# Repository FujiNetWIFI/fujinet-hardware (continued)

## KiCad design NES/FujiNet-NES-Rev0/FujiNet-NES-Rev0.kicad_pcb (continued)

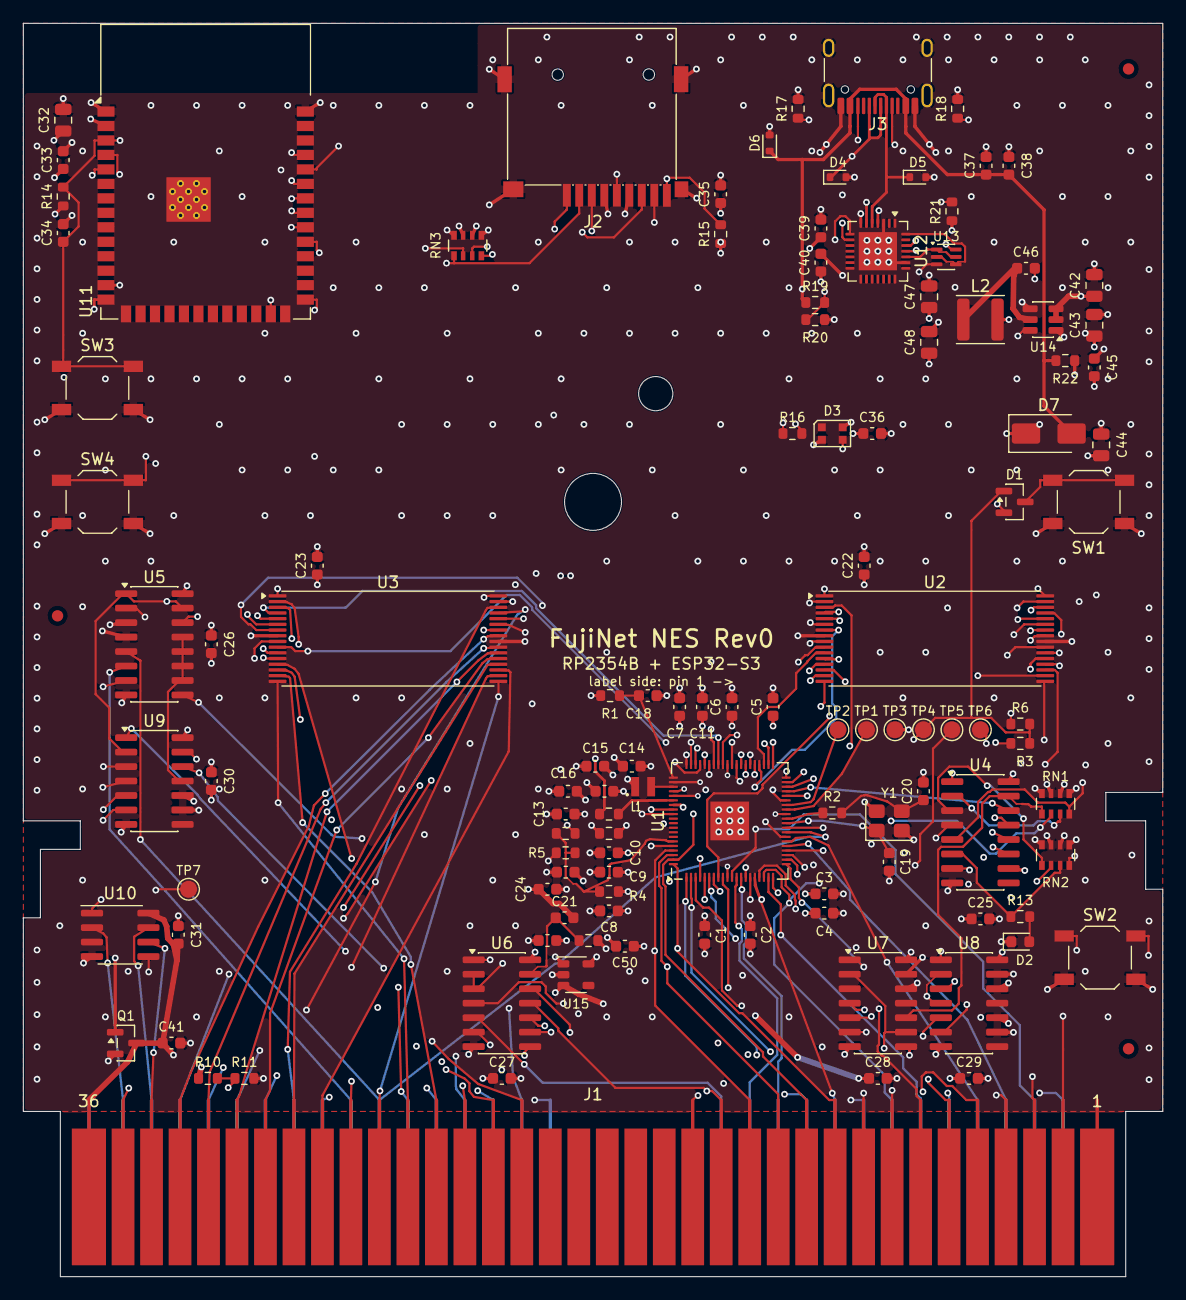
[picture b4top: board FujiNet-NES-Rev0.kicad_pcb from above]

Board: 6 copper layers, 100.0 x 110.0 mm, 118 parts (0 on the bottom side), 148 nets.

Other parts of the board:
FID1, FID2, FID3: Fiducial_1mm_Mask2mm

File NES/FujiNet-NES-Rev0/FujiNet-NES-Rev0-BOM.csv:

"Refs","Value","Footprint","MPN","LCSC","Description","DNP"
"C1,C2,C3,C4,C5,C6,C7,C8,C9,C10,C11,C14,C15,C16,C22,C23,C25,C26,C27,C28,C29,C30,C33,C36,C38,C39,C41,C45,C46","100nF","C_0603_1608Metric","CC0603KRX7R9BB104","C14663","IOVDD decoupling",""
"C12,C24,C35","10uF","C_0603_1608Metric","CL10A106KP8NNNC","C19702","RP IO rail bulk (LDO output)",""
"C13,C17,C18,C40","4.7uF","C_0603_1608Metric","CL10A475KO8NNNC","C19666","VREG_VIN bulk (LDO rail)",""
"C19,C20","15pF","C_0603_1608Metric","CL10C150JB8NNNC","C1644","crystal load",""
"C21,C34,C37,C49,C50","1uF","C_0603_1608Metric","CL10A105KB8NNNC","C15849","'595 power-on hold-off RC",""
"C31","100nF","C_0603_1608Metric","CC0603KRX7R9BB104","C14663","CIClone decoupling","DNP"
"C32,C42,C43,C44,C47,C48","22uF","C_0805_2012Metric","CL21A226MAQNNNE","C45783","S3 bulk (WiFi TX bursts)",""
"D1","BAT54C","SOT-23","BAT54C,215","C37704","RESET steering, common cathode",""
"D2","green","LED_0603_1608Metric","KT-0603G","C12624","activity LED ('595 QG)",""
"D3","WS2812B-2020-V6","LED_WS2812B-2020_PLCC4_2.0x2.0mm","WS2812B-2020-V6","C52917434","status LED on +5V (datasheet VDD 3.7-5.3 V; VIH 2.7 V takes the S3 3.3 V data directly)",""
"D4,D5,D6","ESD5Z5.0T1G","D_SOD-523","ESD5Z5.0T1G","C82044","ESD",""
"D7","SS34","D_SMA","SS34","C8678","USB VBUS OR-ing (no back-feed into the console)",""
"J2","microSD","TF-SMD_TF-015","TF-015","C113206","microSD push-push, SPI mode",""
"J3","USB-C","USB_C_Receptacle_HRO_TYPE-C-31-M-12","TYPE-C-31-M-12","C165948","power + S3 programming",""
"L1","3.3uH","RPI_L_AOTA-B201610S3R3","AOTA-B201610S3R3-101-T","C42411119","RP2350 core SMPS inductor",""
"L2","6.8uH","L_Sunlord_SWPA4030S","SWPA4030S6R8MT","C62684","buck inductor",""
"Q1","AO3401A","SOT-23","AO3401A","C15127","console 5V switch: G = VBUS, S = +5V, D = CONS_5V; body diode CONS_5V -> +5V",""
"R1","33R","R_0603_1608Metric","0603WAF330JT5E","C23140","VREG_AVDD filter",""
"R2,R5,R6,R7,R13","1k","R_0603_1608Metric","0603WAF1001T5E","C21190","crystal drive limit",""
"R3,R4,R14,R15,R21","10k","R_0603_1608Metric","0603WAF1002T5E","C25804","RUN pull-up",""
"R8,R9","27R","R_0603_1608Metric","0603WAF270JT5E","C25190","USB series",""
"R10,R19","22k","R_0603_1608Metric","0603WAF2202T5E","C31850","console 5V sense divider",""
"R11,R12","100k","R_0603_1608Metric","0603WAF1003T5E","C25803","console 5V sense -> 0.82 x CONS_5V",""
"R16","330R","R_0603_1608Metric","0603WAF3300T5E","C23138","WS2812 data series",""
"R17,R18","5.1k","R_0603_1608Metric","0603WAF5101T5E","C23186","UFP Rd",""
"R20","47k","R_0603_1608Metric","0603WAF4702T5E","C25819","VBUS sense divider",""
"R22","4.7k","R_0603_1608Metric","0603WAF4701T5E","C23162","P-FET gate pull-down against the SS34 reverse leakage",""
"RN1,RN2","4x100k","R_Array_Convex_4x0603","4D03WGJ0104T5E","C1996","'595 enables default low while /OE is high",""
"RN3","4x10k","R_Array_Convex_4x0603","4D03WGJ0103T5E","C29718","SD pull-ups",""
"SW1","RESET","SW_SPST_TL3342","TL3342F160QG","C2886898","cart RESET: RP RUN + S3 EN via BAT54C",""
"SW2","BOOTSEL","SW_SPST_TL3342","TL3342F160QG","C2886898","RP2354 BOOTSEL (hold while pressing RESET)",""
"SW3","S3_RST","SW_SPST_TL3342","TL3342F160QG","C2886898","ESP32-S3 EN",""
"SW4","S3_BOOT","SW_SPST_TL3342","TL3342F160QG","C2886898","ESP32-S3 BOOT (IO0)",""
"U1","RP2354B","QFN-80-1EP_10x10mm_P0.4mm_EP3.4x3.4mm","RP2354B","C39843328","RP2350B + 2MB flash in package; cart bus server + bank tables",""
"U2,U3","AS6C4008-55TIN","TSOP-I-32_18.4x8mm_P0.5mm","AS6C4008-55TIN","C5569980","PRG SRAM 512Kx8: $8000-$FFFF through the 4 x 8K bank table (GP33-38)",""
"U4","74HCT595","SOIC-16_3.9x9.9mm_P1.27mm","74HCT595D,118","C282339","control bits: SRAM_EN PRG_WE_EN CHR_WE_EN MIR0 MIR1 FOURSCREEN LED spare",""
"U5","74HCT253","SOIC-16_3.9x9.9mm_P1.27mm","74HCT253D,653","C547509","CIRAM A10 mirroring mux + CIRAM /CE tri-state gate (/OE = PWR_OK_N)",""
"U6","74HCT14","SOIC-14_3.9x8.7mm_P1.27mm","SN74HCT14DR","C6769","PWR_OK / PWR_OK_N from the console 5V sense; ROMSEL, R/W, CHR_WE_EN inversions; POR Schmitt",""
"U7","74HCT20","SOIC-14_3.9x8.7mm_P1.27mm","CD74HCT20M96","C2878717","PRG SRAM /WE = NAND4(M2, ROMSEL, !R/W, PRG_WE_EN); /CE = NAND(ROMSEL, SRAM_EN)",""
"U8","74HCT00","SOIC-14_3.9x8.7mm_P1.27mm","SN74HCT00DR","C6764","PRG SRAM /OE; '595 /OE",""
"U9","74HCT32","SOIC-14_3.9x8.7mm_P1.27mm","74HCT32D,653","C5985","CHR SRAM /OE, /WE; CIRAM /CE (pre-gate)",""
"U10","ATtiny13A-SSU","SOIC-8_3.9x4.9mm_P1.27mm","ATTINY13A-SSUR","C40382","CIClone (10NES key), DNP: PB3=CLK PB0=toMB PB1=toPak PB2=+RST","DNP"
"U11","ESP32-S3-WROOM-1-N16R8","ESP32-S3-WROOM-1","ESP32-S3-WROOM-1-N16R8","C2913202","FujiNet core (fujiversal-nes)",""
"U12","CP2102N-A02-GQFN28","QFN-28-1EP_5x5mm_P0.5mm_EP3.35x3.35mm","CP2102N-A02-GQFN28R","C964632","USB-UART for S3 flashing/console (self-powered)",""
"U13","UMH3N","SOT-363_SC-70-6","UMH3N","C62892","esptool auto-program (DevKitC-1 style)",""
"U14","AP63203WU","TSOT-23-6","AP63203WU-7","C780769","3.3V 2A buck",""
"U15","AP2112K-3.3","SOT-23-5","AP2112K-3.3TRG1","C51118","RP2354B 3.3V LDO (IOVDD, VREG_VIN, VREG_AVDD), 600mA, fast start",""
"Y1","12MHz","Crystal_SMD_3225-4Pin_3.2x2.5mm","ABM8-272-T3","C20625731","",""

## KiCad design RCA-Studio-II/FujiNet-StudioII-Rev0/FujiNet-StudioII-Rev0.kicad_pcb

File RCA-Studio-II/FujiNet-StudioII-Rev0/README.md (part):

# FujiNet-StudioII Rev0

FujiNet for the RCA Studio II, on one cartridge. An RP2354B serves the CDP1802 bus in software. The
ESP32-S3 on the same board is the FujiNet (`fujiversal-studio2`) and the RP2354B's USB host. The
board also carries a microSD, a WS2812 status light, and a USB-C with a CP2102N bridge for flashing
and powering it.

**Status: board routed, JLCPCB package ready** (2026-10-11).
- **Board:** 4 layers, 90.9 x 111.5 mm, fully assembled by JLCPCB on the top side.
- **Outline:** FliP's proven Studio II multicart outline from the insertion edge up, then 28 mm taller
  for the S3 half. Because of that it needs a printed shell; the console's slot is open above.
- **Firmware:** the schematic implements `fujinet-firmware/pico/studio2/firmware/include/s2_cart.h`
  and the S3's `include/pinmap/fujiversal-studio2.h` as they stand.
  - Both firmwares run on it unchanged.
  - One pin-map addition lets the S3 re-flash the RP: see *Firmware follow-ups*.
- **Shell:** a printed two-piece shell, `case/FujiNet-StudioII-Shell.scad`. Its size is estimated,
  not measured on an original: see `case/case-spec.md`.
- **Nothing has been built yet:** see **Before ordering**.

| Check (2026-10-11) | Result |
|---|---|
| Drawing checks (`gen_sch.py`) | every sheet wired; 2 crossings on `cart-bus` (see Glue), 1 on `usb` (the auto-program pair), 0 on `rp-core`, `fujinet`, `power` |
| Netlist parity, kicad-cli netlist vs `design.py`, names included | 97 / 97 nets |
| KiCad ERC, all severities | 0 errors, 0 warnings |
| `tools/check_nets.py`: the netlist against `s2_cart.h` and `fujiversal-studio2.h` | 364 checks, 0 failed, 1 warning (*Firmware follow-ups*). Covers the edge map, series R, pull-ups, senses, PWR_OK gating, the power mux and the buck, RP support, the RP <-> S3 USB link and RUN / BOOTSEL forcing, the S3's pins and strapping, the USB-C bridge, and the edge footprint. |
| `tools/check_glue.py`: the '541 enables and CART CS vs `s2_glue_drive()` / `s2_glue_cartcs()`, compiled | 16 / 16 joint input combinations, 0 mismatches. RP unpowered: 4 / 4 silent. Console off: 8 / 8 silent. |
| `tools/audit/edge_orientation.py`: the edge against FliP's board file, EJK's pinout and the original board | all checks pass |
| KiCad DRC + schematic parity, all severities (`route_board.sh`) | 0 violations, 0 unconnected, 0 parity issues, on the saved zone fills (`tools/fill_zones.py` refills them after the last copper change) |
| `tools/check_vias.py`: no via in a foreign SMD pad | 689 vias, 0 failures |
| `tools/audit/layout_checks.py`: the layout's datasheet claims, measured on the copper | 65 / 65 claims hold. Covers the regulator corner, the supply rings, decoupling, USB, crystal, exposed pads, the edge's copper, the S3's antenna keep-out, its decoupling, the buck's input loop. |
| `tools/audit/check_fab.py` (+ `check_gerbers.py`): BOM / CPL / drills / order-number spot / the gerbers | 10 / 10. `check_gerbers.py`: 0 failures, including check 9: no plated hole inside an inner-layer pour of another net |
| `tools/audit/margins.py`: levels, the mux on each source, PWR_OK, pull-ups, LDO, buck, S3 rail, WS2812, CP2102N, crystal, LED | all positive |
| JLCPCB CPL rotations (`tools/audit/jlc/`), measured pad by pad against each part's EasyEDA footprint | 42 / 42 pairs |
| JLCPCB stock, every assembled line (`docs/sourcing.md`) | 44 / 44 in stock for 5 boards. The RP2350 core inductor is down to 24. |
| kicad-happy review (`docs/design-review-rev0.md`) | Ready to order as a bring-up prototype; no blockers. SPICE 15 / 15. Deep review: 32 findings, 32 verified, 0 quarantined. Release gate: 10 pass, 2 waived (board-only parts, layer extents). Three warnings: the 7805 load with WiFi, the S3 pin map, L1 stock. |

## Sheets

| Page | Sheet | Contents |
|---|---|---|
| 1 | root | block diagram, notes. The RP <-> S3 USB pair, RUN / BOOTSEL controls, S3_EN, S3_IO0 and the UART are wired here. |
| 2 | `cart-bus` | 22-pin edge, 330R into GPIO0-9, 74HCT541, CART CS NOR, the PWR_OK-gating ORs, /DRIVE and /CLAIM pull-ups, PWR_OK, ADC sense, LED, debug UART, scope pads |
| 3 | `rp-core` | RP2354B supplies and decoupling, core regulator, crystal, SWD, RUN / BOOTSEL (buttons and the S3's controls), RESET (both MCUs), USB 27R |
| 4 | `fujinet` | ESP32-S3-WROOM-1-N16R8, its EN RC and buttons, microSD, WS2812 |
| 5 | `usb` | USB-C, USBLC6-2SC6, CP2102N, esptool's auto-program pair |
| 6 | `power` | TPS2116 power mux (USB first, console 5 V second), the S3's AP63203 buck, the RP's AP2112K LDO |

Each bus line is one straight wire from the edge to the RP. The edge symbol, the '541 and the RP's
GPIO unit are built on the same rows: D7 is on the top row, and the '541 takes its channels reversed
for the board.

## Edge connector

| Pin | Signal | Net | Pin | Signal | Net |
|---|---|---|---|---|---|
| 1-5 | D7-D3 | '541 Y | 12-14 | MA1-MA3 | 330R -> GPIO1-3 |
| 6 | ROM DISABLE | GND (removes the built-in games, as a cart does) | 15 | +5 V (console 7805) | CONS_5V |
| 7 | GND | GND | 16-18 | MA4-MA6 | 330R -> GPIO4-6 |
| 8-10 | D2-D0 | '541 Y | 19 | TPA (gated by /MRD in the console) | 330R -> GPIO8 |
| 11 | MA0 | 330R -> GPIO0 | 20 | MA7 | 330R -> GPIO7 |
| | | | 21 | /MRD | '541 /OE1, NOR, 330R -> GPIO9 |
| | | | 22 | CART CS (cart output, high = console RAM off) | NOR output |

The pinout is EJK's console schematic. FliP's multicart board carries the same signals on the same
pads, and `tools/audit/edge_orientation.py` compares them pad by pad. There is no write strobe,
clock or reset on the edge.

**The geometry is FliP's** (Philip Marien's RCA Studio II multicart v5.1, github.com/vodkaflip/
RCA_Studio_II). It was read from his Eagle board file and fab gerbers into `tools/edge_geom.py`. The
board is built, runs in real consoles and fits original shells, and photos of an original game
board match its outline.

- **22 contacts on one face, B.Cu**, at 0.156" (3.9624 mm):
  - 1.905 mm wide, with copper 0.70-8.95 mm from the edge;
  - each in its own mask opening;
  - hard gold with a 45-degree bevel.
  The console's CN1 is a 2x22 connector whose lettered row is unconnected (EJK).
- **Pin 1 (D7) is at the left seen from the contact face**, so at the right seen from the parts
  (F.Cu). The contacts face the back of the console, the parts its front, as on an original cart.
- **No tab:** the full 90.912 mm bottom edge enters the slot. Up to the top of FliP's straight sides
  the board is his:
  - two 8.128 mm holes 68.58 mm in, where the original shell's posts go;
  - a half-round notch in each side 20.83 mm in.
- **Above that the board grows 28 mm** (111.49 mm overall, rounded top corners) for the ESP32-S3
  half, so it needs a printed shell.
- **1.6 mm thick** (FliP's boards are 1.57 mm).
- **No part closer than 23.5 mm to the edge.** That band holds the finger stubs, the address bus's
  twist and the data bus's fan-in, and it enters the console under the shell.
- **FliP's holes and notches** sit ~0.24 mm off-centre in opposite directions (hand-placed). The
  holes keep his positions, mirrored because he drew from the contact face. Both notches take his
  deeper cut.

## RP2354B pin map

Exactly `s2_cart.h`. `check_nets.py` reads every `*_PIN` and fails if the header names a pin this
board does not wire, or the board wires one the header does not name.

| GPIO | Net | Goes to |
|---|---|---|
| 0-7 | RP_MA0-7 | 330R -> edge MA0-MA7 |
| 8 | RP_TPA | 330R -> edge 19 |
| 9 | RP_MRD | 330R -> edge 21 |
| 16-23 | RP_D0-7 | 74HCT541 A8-A1, channels reversed (A8 / Y8 = bit 0: the board's data bus is then planar) (outputs only) |
| 24 | DRIVE_N | 74HCT32 -> '541 /OE2; R11 10k to +5V |
| 25 | CLAIM_N | 74HCT32 -> NOR; R12 10k to +5V |
| 26 | PWR_OK | 74HCT14, two stages from the console 5 V; the first stage (PWR_OK_N) gates the ORs |
| 27 | RP_LED | 1k, red LED |
| 40 | VSENSE_ADC | ADC0: edge 15 through 100k / 100k (0.5 x), 100 nF |
| 44, 45 | DBG_TX, DBG_RX | J2 (DNP), 3.3 V only |
| USB | RP_USB_DP / DM | 27R -> the ESP32-S3's USB host (IO20 / IO19), on the board |
| RUN, QSPI_SS | RUN, QSPI_SS | the buttons, and the S3's IO4 / IO5 through 1k |

- The console's lines reach the RP through 330R. That limits the current into a 5 V-tolerant pad
  while IOVDD is still rising, and costs under 2 ns.
- GPIO40-47 are not 5 V tolerant. `check_nets.py` asserts only passives and the debug header reach
  them.
- No bus pin has a pull: the firmware turns the pad pulls off (RP2350-E9).

## ESP32-S3 pin map

Exactly `fujiversal-studio2.h`. `check_nets.py` reads it and checks every pin.

| S3 pin | Net | Goes to |
|---|---|---|
| IO19 / IO20 | USB_DM / USB_DP | the RP2354B's USB through its 27R (the S3 is the host) |
| IO38 / IO39 / IO40 / IO41 | SD_MOSI / SD_SCK / SD_MISO / SD_CS | microSD (SPI mode), 10k pull-ups on CS, DO, DAT1, DAT2 |
| IO42 | SD_CD | card detect, 10k pull-up (low = card in) |
| IO48 | LED_STRIP | 330R -> WS2812B-2020 (on +5V; VIH 2.7 V takes 3.3 V data) |
| TXD0 / RXD0 (IO43 / 44) | S3_TXD / S3_RXD | CP2102N (flashing and the S3's console over the USB-C) |
| IO4 / IO5 | RUN_CTL / BOOTSEL_CTL | 1k -> RP RUN / QSPI_SS: the S3 can reset the RP into its USB boot ROM |
| EN | S3_EN | 10k / 1 uF power-on delay; S3_RST button, the cart RESET (through the BAT54C), the auto-program pair |
| IO0 | S3_IO0 | S3_BOOT button, the auto-program pair |
| IO3, IO45, IO46 | -- | strapping pins, unloaded |

The N16R8 module's octal PSRAM takes IO35-37, and its flash takes IO26-32. Neither is used.

## Glue

```
'541 drives D0-D7  = !/MRD & !/DRIVE & PWR_OK                    (s2_glue_drive)
                     /OE1 = /MRD          /OE2 = /DRIVE | PWR_OK_N     74HCT32
CART CS            = NOR(/MRD, /CLAIM) & PWR_OK                  (s2_glue_cartcs)
                   = NOR(/MRD, /CLAIM | PWR_OK_N)                    74HCT32 + 74HCT1G02
```

- /MRD alone ends a read in hardware, for both outputs. It is the '541's /OE1 with no gate between
  them, and one gate from CART CS.
- **The console's power gates both outputs.** With the console off, PWR_OK_N (the first '14 stage)
  is high, so nothing is driven into it: not D0-D7, not CART CS.
  - This holds whatever the RP, running from USB, has left on /DRIVE and /CLAIM.
  - The gates run on +5V, the cart's own muxed rail, so they work with the console off.
- No 74HCT27 (triple 3-input NOR) is stocked at JLCPCB, so the 3-input NOR is a '32 OR into the
  '1G02. The '32's other gate makes /OE2.
- The '541, '32 and NOR run on +5V, so D0-D7 and CART CS are 5 V CMOS levels; the 1802's VIH is
  3.5 V at 5 V. Their TTL inputs take the RP's 3.3 V.
- R11 / R12 hold /DRIVE and /CLAIM high, keeping the cart silent while the RP is unpowered or
  booting. 10k beats the RP2350's reset pull-down. `check_glue.py` checks this and the console-off
  case.
- `cart-bus` has two crossings, both forced:
  - the /MRD riser crosses /OE2, because /OE1 = /MRD sits between the '541's A pins and /OE2;
  - PWR_OK_N crosses the /MRD line once, because it reaches one OR above that line and one below.

## Power

- **U10, TPS2116 power mux: +5V.** VIN1 is the USB-C's VBUS, VIN2 the console's 5 V (CONS_5V, edge 15).
  - **Priority:** MODE is tied to VIN1, and PR1 comes from a 33k / 10k divider. VBUS above
    3.96-4.64 V (always, for a USB source) runs the cart, and the console's 7805 then supplies
    nothing. Otherwise the console does.
  - **Drop:** 37-60 mOhm either way. +5V sits within ~30 mV of its source at the cart's peak, so the
    74HCT glue stays inside its 4.5-5.5 V on either source (`tools/audit/margins.py`: >= 4.72 V).
  - **Reverse-current blocking:** neither source back-feeds the other. Switchover is
    break-before-make (~8 us), and +5V's 50 uF carries the cart through it.
- **+5V feeds:**
  - the '541, '32, '1G02 and '14;
  - the WS2812;
  - U12, an AP2112K, giving +3V3: every RP2354B supply pin. It rises with +5V, so the 5 V-tolerant
    pads are never unpowered with 5 V on them;
  - U11, an AP63203 2 A buck, giving +3V3_S3: the ESP32-S3, the CP2102N and the microSD.
- **Load:** ~140 mA average with the S3 on WiFi, ~470 mA peak (`margins.py`).
  - With USB-C connected, all of it comes from USB.
  - With no USB, all of it comes from the console's 7805. Its headroom is unmeasured: bring-up step 2.
- **USB-C:**
  - a UFP (5.1k Rd on CC1 / CC2), behind a USBLC6-2SC6 (3.5 pF per line);
  - its D+ / D- go to the CP2102N, which flashes the S3 and carries its console;
  - the RP's USB is the S3's (on the board), not the receptacle's.

## Parts

Every part is JLCPCB-assemblable. The stock below is from JLCPCB's parts library on 2026-10-11
(`docs/sourcing.md`, `tools/audit/sourcing.py`). `FujiNet-StudioII-Rev0-BOM.csv` has every line with
MPN, manufacturer and LCSC code.

| Part | LCSC | JLC stock | Note |
|---|---|---|---|
| RP2354B | C39843328 | 3640 | extended |
| ESP32-S3-WROOM-1-N16R8 | C2913202 | 34k | extended; the FujiNet module (16 MB flash, 8 MB PSRAM) |
| SN74HCT541PWR | C436096 | 25k | extended |
| 74HCT1G02GV,125 (Nexperia, SOT-753) | C12504 | 2.9k | extended. Fallback: SN74AHCT1G02DBVR, C163710, same SOT-23-5 land (A / B swapped, which a NOR does not care about) |
| SN74HCT14DR, SN74HCT32DR | C6769, C6781 | 36k, 3.0k | extended |
| TPS2116DRLR (power mux) | C3235557 | 75k | extended |
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
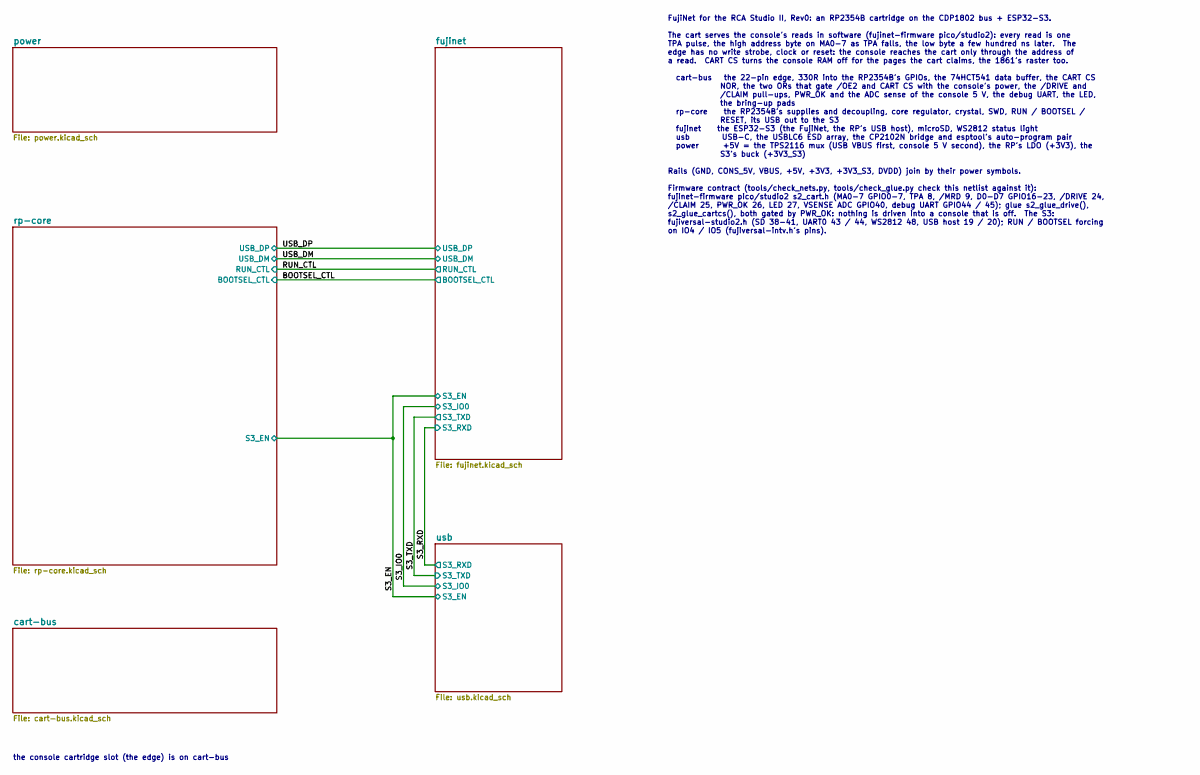
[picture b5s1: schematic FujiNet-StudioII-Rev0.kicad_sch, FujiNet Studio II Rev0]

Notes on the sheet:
the console cartridge slot (the edge) is on cart-bus
FujiNet for the RCA Studio II, Rev0: an RP2354B cartridge on the CDP1802 bus + ESP32-S3. The cart serves the console's reads in software (fujinet-firmware pico/studio2): every read is one TPA pulse, the high address byte on MA0-7 as TPA falls, the low byte a few hundred ns later. The edge has no wr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

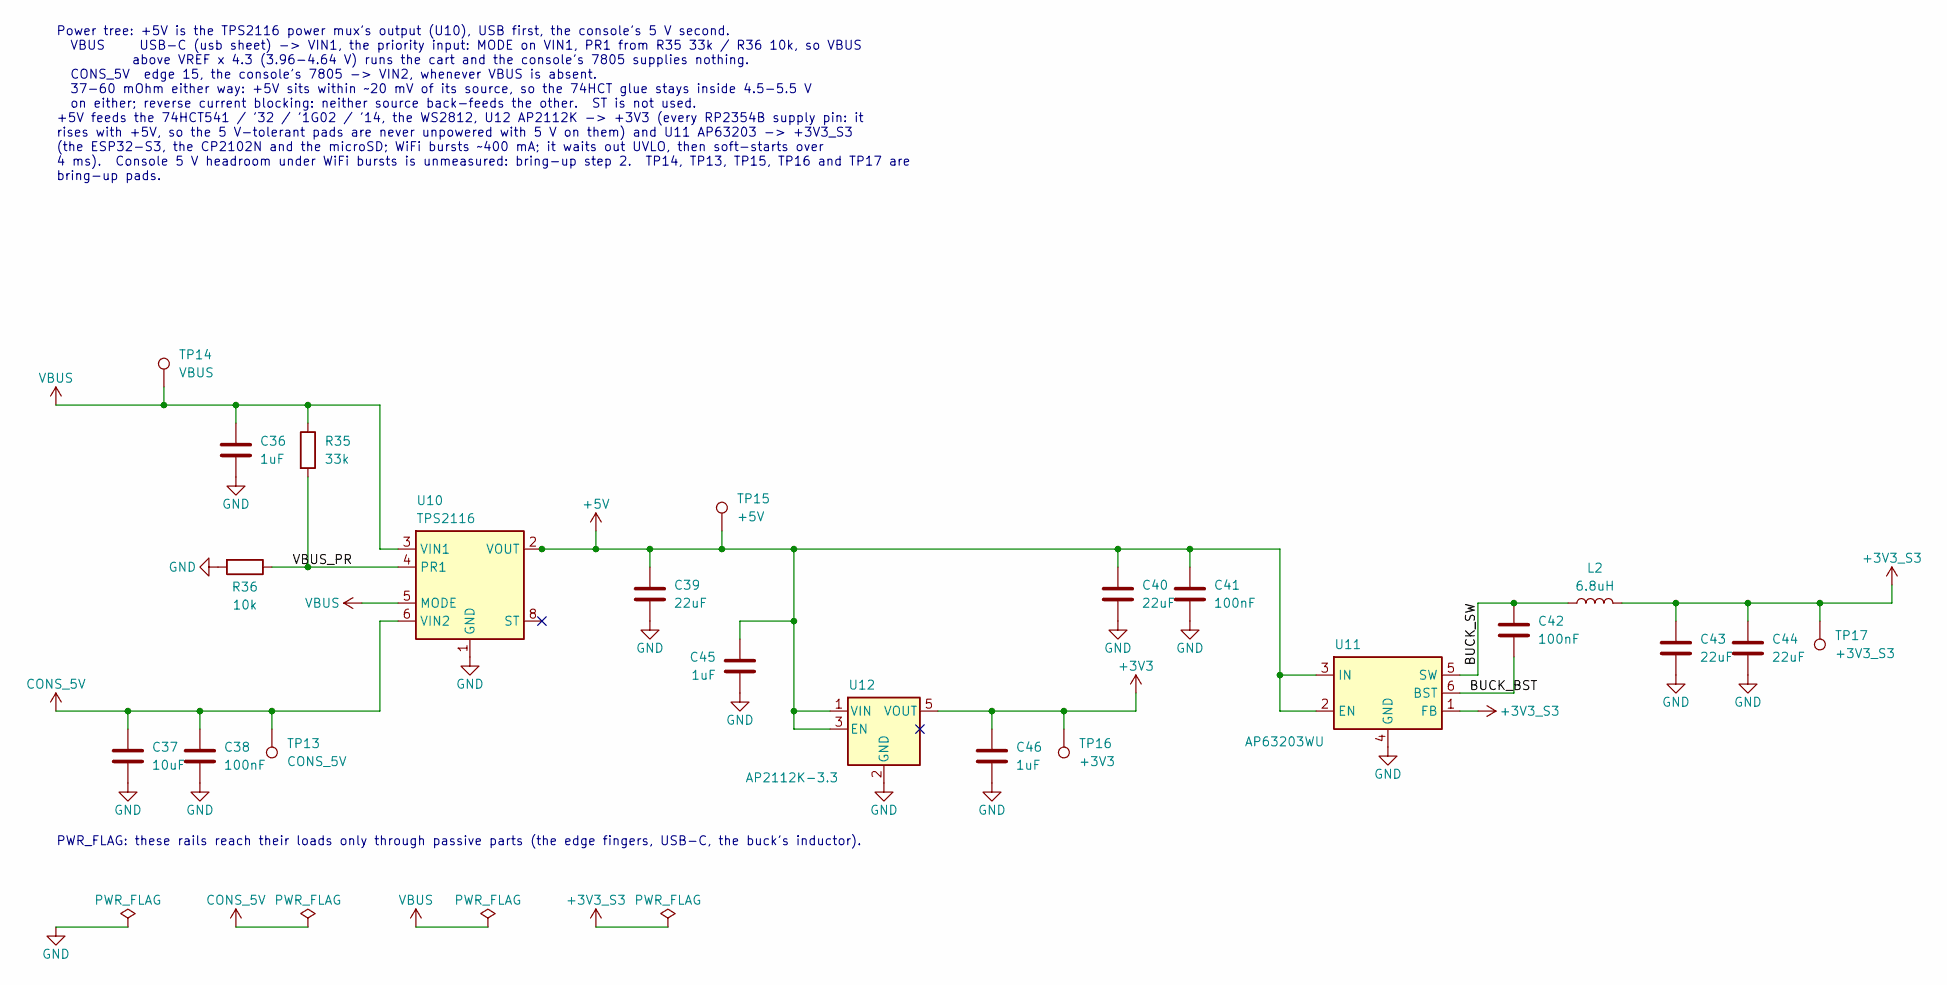
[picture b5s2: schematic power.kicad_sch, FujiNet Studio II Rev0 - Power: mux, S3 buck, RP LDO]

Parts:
C36, C45, C46: 1uF; C_0603_1608Metric; MPN CL10A105KB8NNNC; LCSC C15849
C37: 10uF; C_0603_1608Metric; MPN CL10A106KP8NNNC; LCSC C19702
C38, C41, C42: 100nF; C_0603_1608Metric; MPN CC0603KRX7R9BB104; LCSC C14663
C39, C40, C43, C44: 22uF; C_0805_2012Metric; MPN CL21A226MAQNNNE; LCSC C45783
L2: 6.8uH; L_Sunlord_SWPA4030S; MPN SWPA4030S6R8MT; LCSC C62684
R35: 33k; R_0603_1608Metric; MPN 0603WAF3302T5E; LCSC C4216
R36: 10k; R_0603_1608Metric; MPN 0603WAF1002T5E; LCSC C25804
TP13: CONS_5V; TestPoint_Pad_D1.5mm
TP14: VBUS; TestPoint_Pad_D1.5mm
TP15: +5V; TestPoint_Pad_D1.5mm
TP16: +3V3; TestPoint_Pad_D1.5mm
TP17: +3V3_S3; TestPoint_Pad_D1.5mm
U10: TPS2116; SOT-583-8; MPN TPS2116DRLR; LCSC C3235557
U11: AP63203WU; TSOT-23-6; MPN AP63203WU-7; LCSC C780769
U12: AP2112K-3.3; SOT-23-5; MPN AP2112K-3.3TRG1; LCSC C51118

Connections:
+3V3: C46.1, TP16.1, U12.5 (VOUT); also elsewhere on the board
+3V3_S3: C43.1, C44.1, L2.2, TP17.1, U11.1 (FB); also elsewhere on the board
+5V: C39.1, C40.1, C41.1, C45.1, TP15.1, U10.2 (VOUT), U10.7 (VOUT), U11.2 (EN), U11.3 (IN), U12.1 (VIN), U12.3 (EN); also elsewhere on the board
/power/BUCK_BST: C42.2, U11.6 (BST)
/power/BUCK_SW: C42.1, L2.1, U11.5 (SW)
/power/VBUS_PR: R35.2, R36.1, U10.4 (PR1)
CONS_5V: C37.1, C38.1, TP13.1, U10.6 (VIN2); also elsewhere on the board
GND: C36.2, C37.2, C38.2, C39.2, C40.2, C41.2, C43.2, C44.2, C45.2, C46.2, R36.2, U10.1 (GND), U11.4 (GND), U12.2 (GND); also elsewhere on the board
VBUS: C36.1, R35.1, TP14.1, U10.3 (VIN1), U10.5 (MODE); also elsewhere on the board

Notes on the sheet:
PWR_FLAG: these rails reach their loads only through passive parts (the edge fingers, USB-C, the buck's inductor).
Power tree: +5V is the TPS2116 power mux's output (U10), USB first, the console's 5 V second. VBUS USB-C (usb sheet) -> VIN1, the priority input: MODE on VIN1, PR1 from R35 33k / R36 10k, so VBUS above VREF x 4.3 (3.96-4.64 V) runs the cart and the console's 7805 supplies nothing. CONS_5V edge 15, 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

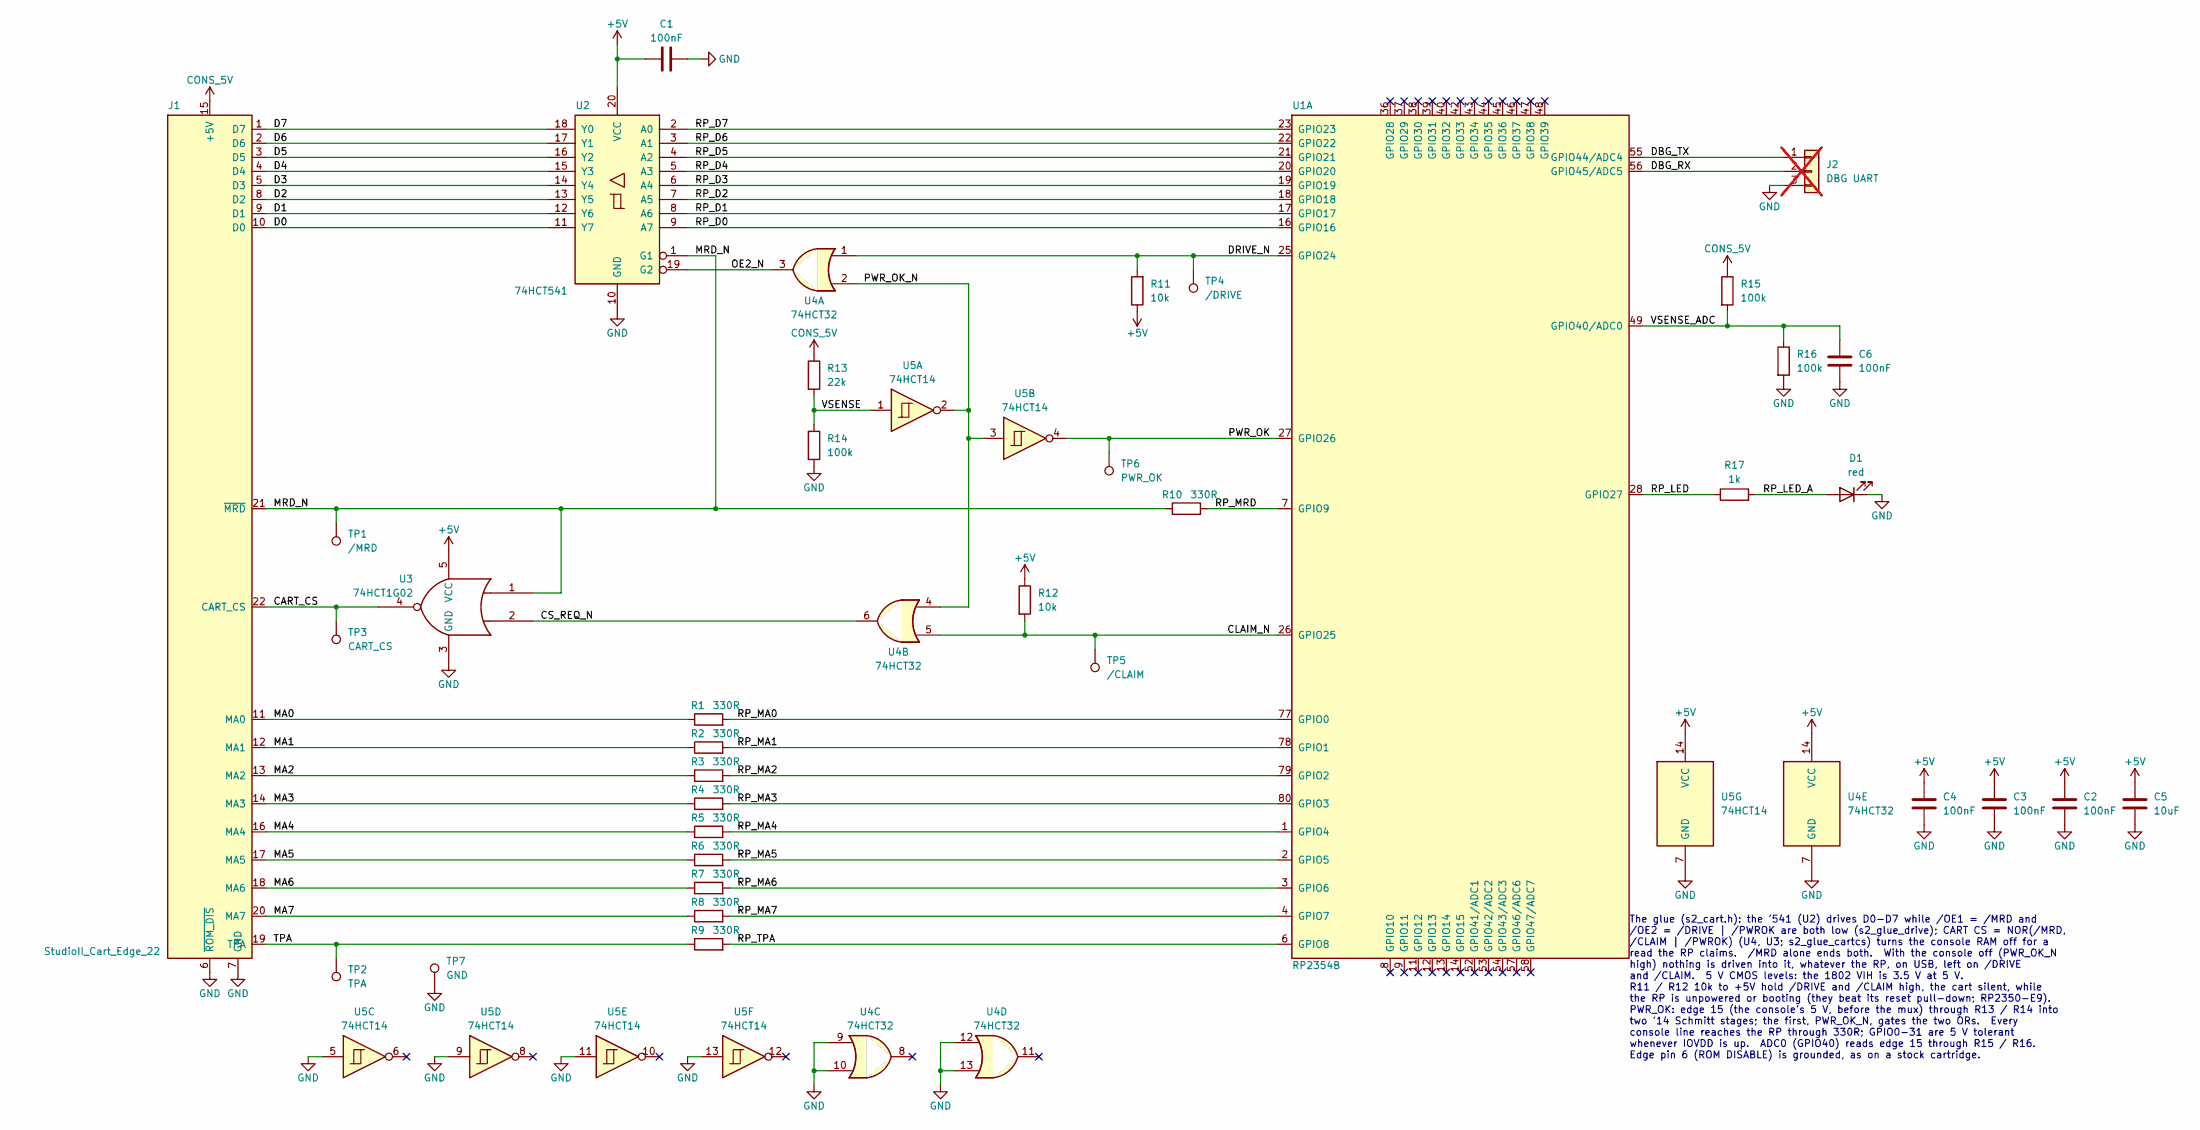
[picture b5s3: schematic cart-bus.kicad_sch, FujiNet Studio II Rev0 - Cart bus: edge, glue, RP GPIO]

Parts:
C1, C2, C3, C4, C6: 100nF; C_0603_1608Metric; MPN CC0603KRX7R9BB104; LCSC C14663
C5: 10uF; C_0603_1608Metric; MPN CL10A106KP8NNNC; LCSC C19702
D1: red; LED_0603_1608Metric; MPN KT-0603R; LCSC C2286
J1: StudioII_Cart_Edge_22
J2: DBG UART; PinHeader_1x03_P2.54mm_Vertical; MPN PZ254V-11-03P; LCSC C2937625; not fitted
R1, R2, R3, R4, R5, R6, R7, R8, R9, R10: 330R; R_0603_1608Metric; MPN 0603WAF3300T5E; LCSC C23138
R11, R12: 10k; R_0603_1608Metric; MPN 0603WAF1002T5E; LCSC C25804
R13: 22k; R_0603_1608Metric; MPN 0603WAF2202T5E; LCSC C31850
R14, R15, R16: 100k; R_0603_1608Metric; MPN 0603WAF1003T5E; LCSC C25803
R17: 1k; R_0603_1608Metric; MPN 0603WAF1001T5E; LCSC C21190
TP1: /MRD; TestPoint_Pad_D1.5mm
TP2: TPA; TestPoint_Pad_D1.5mm
TP3: CART_CS; TestPoint_Pad_D1.5mm
TP4: /DRIVE; TestPoint_Pad_D1.5mm
TP5: /CLAIM; TestPoint_Pad_D1.5mm
TP6: PWR_OK; TestPoint_Pad_D1.5mm
TP7: GND; TestPoint_Pad_D1.5mm
U1: RP2354B; QFN-80-1EP_10x10mm_P0.4mm_EP3.4x3.4mm; MPN RP2354B; LCSC C39843328
U2: 74HCT541; TSSOP-20_4.4x6.5mm_P0.65mm; MPN SN74HCT541PWR; LCSC C436096
U3: 74HCT1G02; SOT-23-5; MPN 74HCT1G02GV,125; LCSC C12504
U4: 74HCT32; SOIC-14_3.9x8.7mm_P1.27mm; MPN SN74HCT32DR; LCSC C6781
U5: 74HCT14; SOIC-14_3.9x8.7mm_P1.27mm; MPN SN74HCT14DR; LCSC C6769

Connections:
+5V: C1.1, C2.1, C3.1, C4.1, C5.1, R11.1, R12.1, U2.20 (VCC), U3.5 (VCC), U4.14 (VCC), U5.14 (VCC); also elsewhere on the board
/cart-bus/CART_CS: J1.22 (CART_CS), TP3.1, U3.4
/cart-bus/CLAIM_N: R12.2, TP5.1, U1.26 (GPIO25), U4.5
/cart-bus/CS_REQ_N: U3.2, U4.6
/cart-bus/D0: J1.10 (D0), U2.11 (Y7)
/cart-bus/D1: J1.9 (D1), U2.12 (Y6)
/cart-bus/D2: J1.8 (D2), U2.13 (Y5)
/cart-bus/D3: J1.5 (D3), U2.14 (Y4)
/cart-bus/D4: J1.4 (D4), U2.15 (Y3)
/cart-bus/D5: J1.3 (D5), U2.16 (Y2)
/cart-bus/D6: J1.2 (D6), U2.17 (Y1)
/cart-bus/D7: J1.1 (D7), U2.18 (Y0)
/cart-bus/DBG_RX: J2.2, U1.56 (GPIO45/ADC5)
/cart-bus/DBG_TX: J2.1, U1.55 (GPIO44/ADC4)
/cart-bus/DRIVE_N: R11.2, TP4.1, U1.25 (GPIO24), U4.1
/cart-bus/MA0: J1.11 (MA0), R1.1
/cart-bus/MA1: J1.12 (MA1), R2.1
/cart-bus/MA2: J1.13 (MA2), R3.1
/cart-bus/MA3: J1.14 (MA3), R4.1
/cart-bus/MA4: J1.16 (MA4), R5.1
/cart-bus/MA5: J1.17 (MA5), R6.1
/cart-bus/MA6: J1.18 (MA6), R7.1
/cart-bus/MA7: J1.20 (MA7), R8.1
/cart-bus/MRD_N: J1.21 (~MRD), R10.1, TP1.1, U2.1 (G1), U3.1
/cart-bus/OE2_N: U2.19 (G2), U4.3
/cart-bus/PWR_OK: TP6.1, U1.27 (GPIO26), U5.4
/cart-bus/PWR_OK_N: U4.2, U4.4, U5.2, U5.3
/cart-bus/RP_D0: U1.16 (GPIO16), U2.9 (A7)
/cart-bus/RP_D1: U1.17 (GPIO17), U2.8 (A6)
/cart-bus/RP_D2: U1.18 (GPIO18), U2.7 (A5)
/cart-bus/RP_D3: U1.19 (GPIO19), U2.6 (A4)
/cart-bus/RP_D4: U1.20 (GPIO20), U2.5 (A3)
/cart-bus/RP_D5: U1.21 (GPIO21), U2.4 (A2)
/cart-bus/RP_D6: U1.22 (GPIO22), U2.3 (A1)
/cart-bus/RP_D7: U1.23 (GPIO23), U2.2 (A0)
/cart-bus/RP_LED: R17.1, U1.28 (GPIO27)
/cart-bus/RP_LED_A: D1.2 (A), R17.2
/cart-bus/RP_MA0: R1.2, U1.77 (GPIO0)
/cart-bus/RP_MA1: R2.2, U1.78 (GPIO1)
/cart-bus/RP_MA2: R3.2, U1.79 (GPIO2)
/cart-bus/RP_MA3: R4.2, U1.80 (GPIO3)
/cart-bus/RP_MA4: R5.2, U1.1 (GPIO4)
/cart-bus/RP_MA5: R6.2, U1.2 (GPIO5)
/cart-bus/RP_MA6: R7.2, U1.3 (GPIO6)
/cart-bus/RP_MA7: R8.2, U1.4 (GPIO7)
/cart-bus/RP_MRD: R10.2, U1.7 (GPIO9)
/cart-bus/RP_TPA: R9.2, U1.6 (GPIO8)
/cart-bus/TPA: J1.19 (TPA), R9.1, TP2.1
/cart-bus/VSENSE: R13.2, R14.1, U5.1
/cart-bus/VSENSE_ADC: C6.1, R15.2, R16.1, U1.49 (GPIO40/ADC0)
CONS_5V: J1.15 (+5V), R13.1, R15.1; also elsewhere on the board
GND: C1.2, C2.2, C3.2, C4.2, C5.2, C6.2, D1.1 (K), J1.6 (~ROM_DIS), J1.7 (GND), J2.3, R14.2, R16.2, TP7.1, U2.10 (GND), U3.3 (GND), U4.7 (GND), U4.9, U4.10, U4.12, U4.13, U5.5, U5.7 (GND), U5.9, U5.11, U5.13; also elsewhere on the board

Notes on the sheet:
The glue (s2_cart.h): the '541 (U2) drives D0-D7 while /OE1 = /MRD and /OE2 = /DRIVE | /PWROK are both low (s2_glue_drive); CART CS = NOR(/MRD, /CLAIM | /PWROK) (U4, U3; s2_glue_cartcs) turns the console RAM off for a read the RP claims. /MRD alone ends both. With the console off (PWR_OK_N high) no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

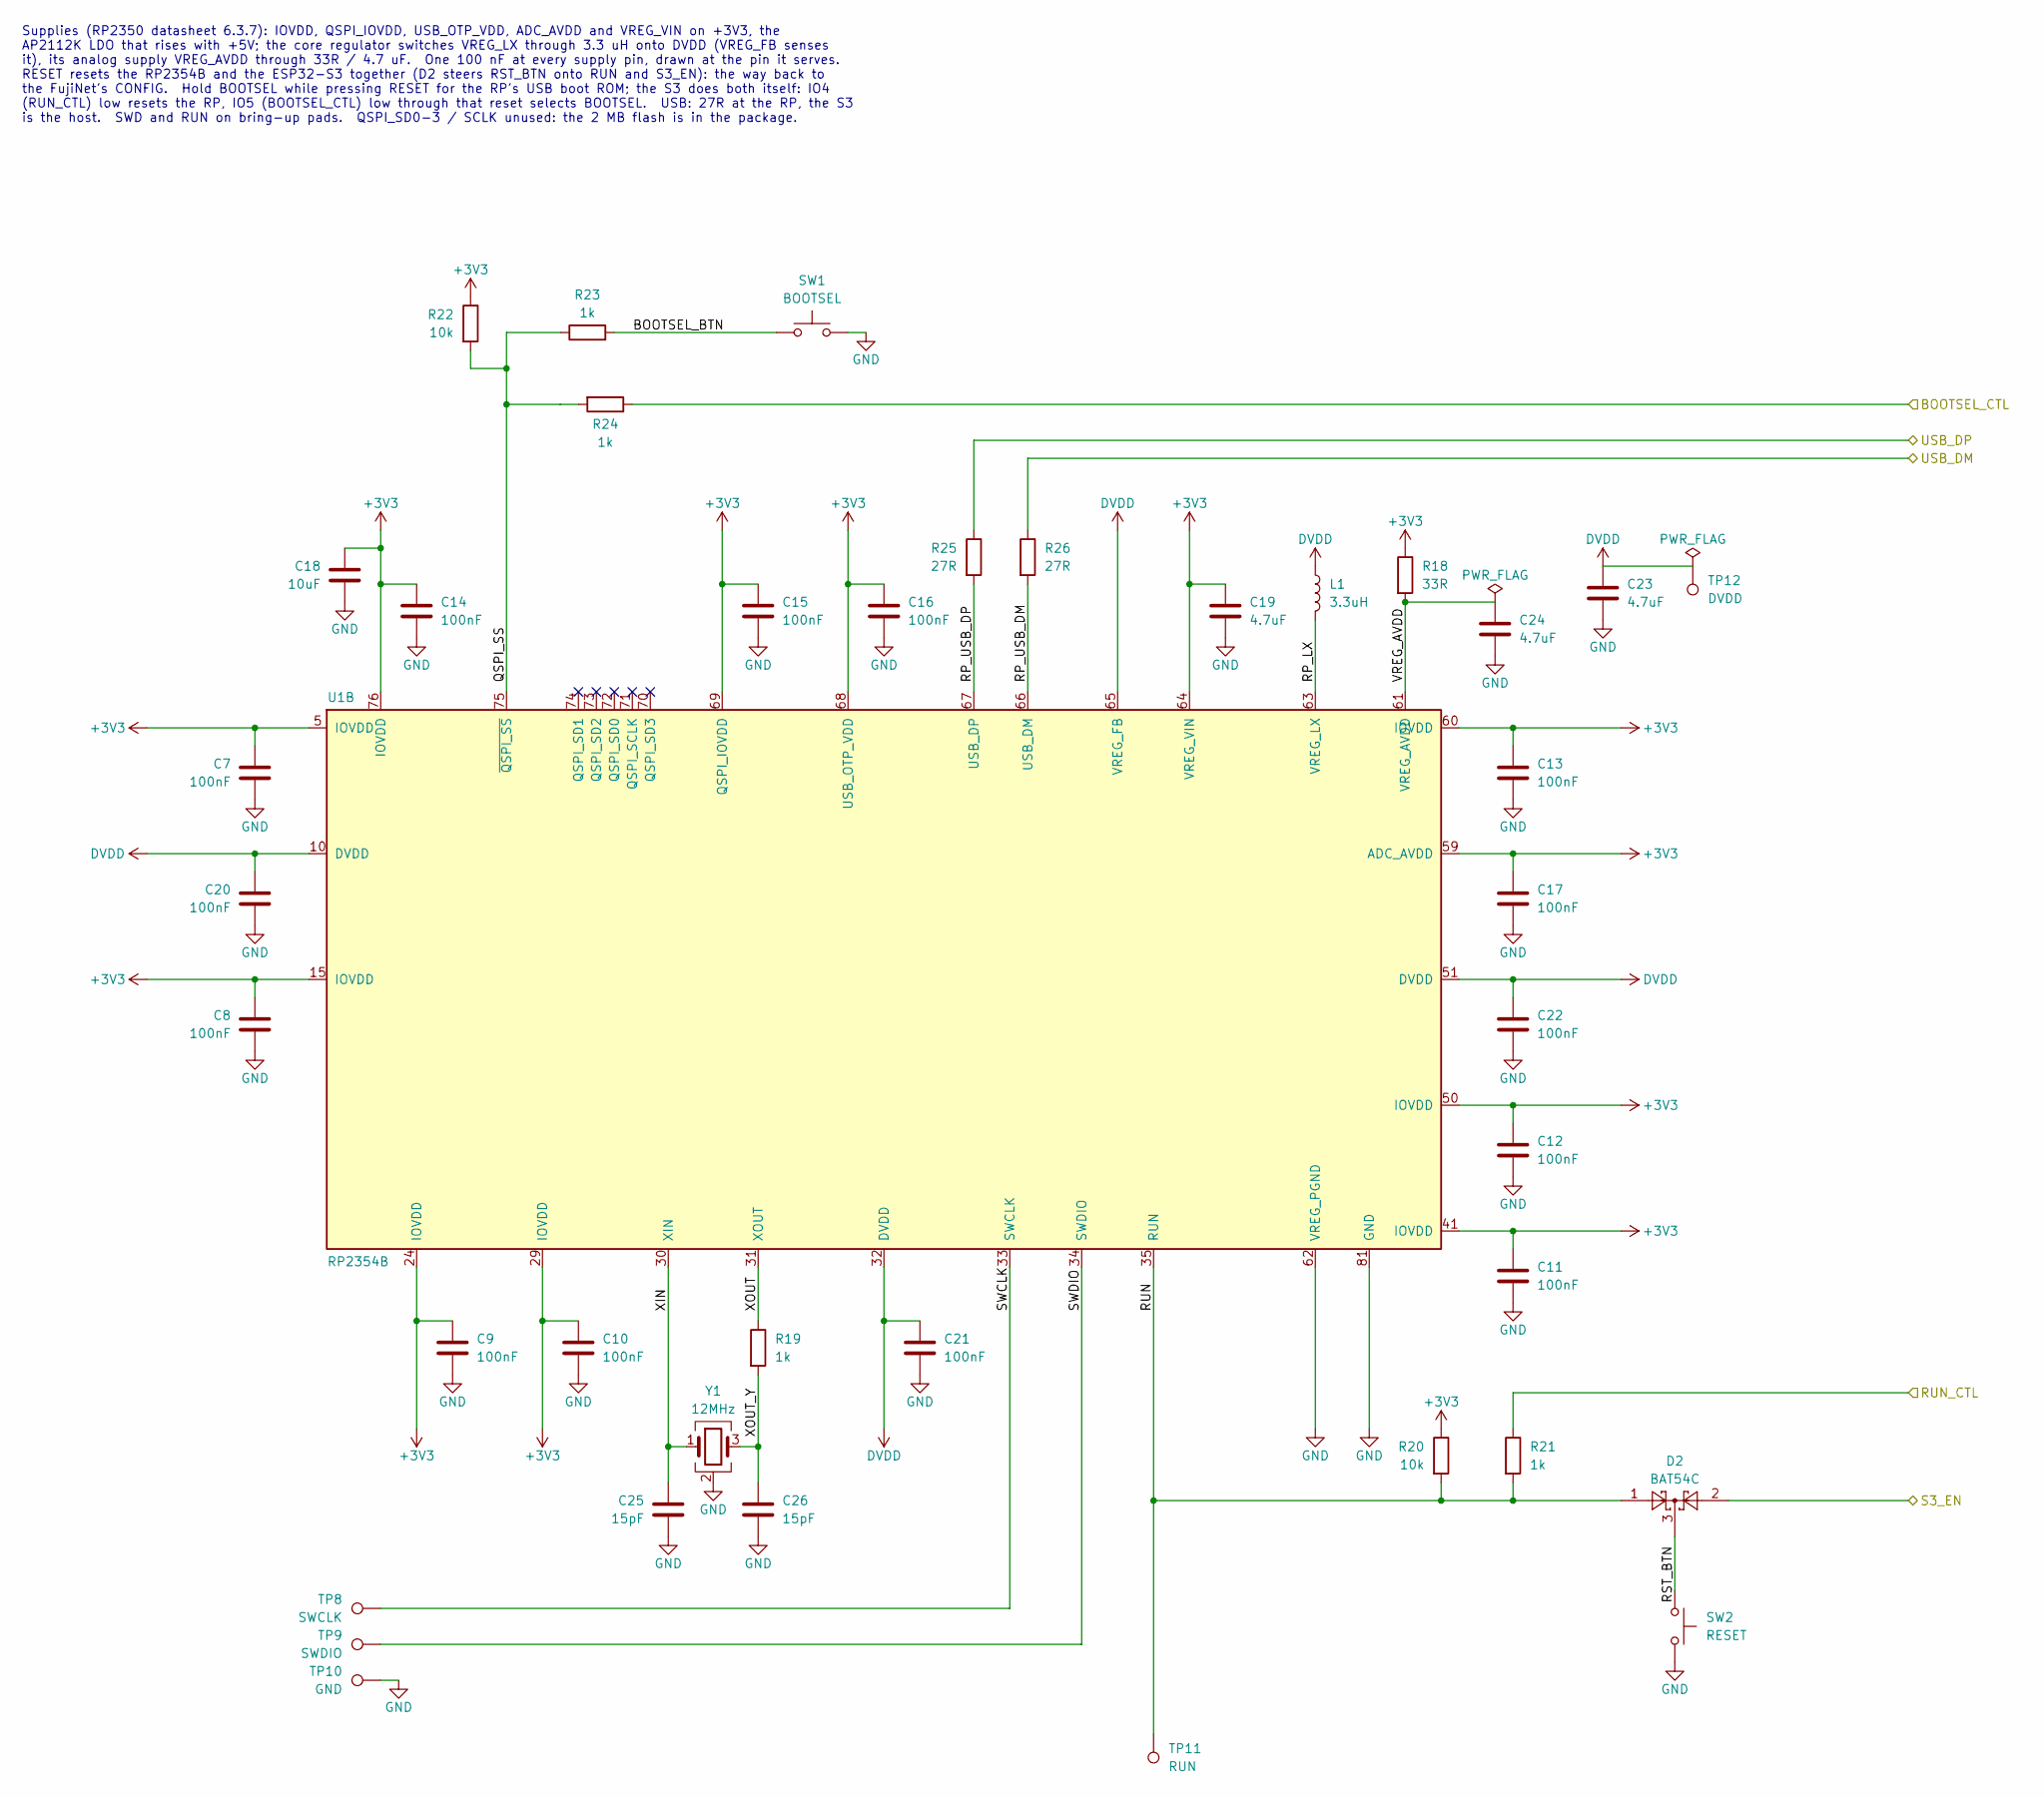
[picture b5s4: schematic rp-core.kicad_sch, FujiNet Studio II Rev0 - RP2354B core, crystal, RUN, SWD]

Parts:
C7, C8, C9, C10, C11, C13, C14, C15, C17, C20, C21: 100nF; C_0603_1608Metric; MPN CC0603KRX7R9BB104; LCSC C14663
C12, C16, C22: 100nF; RPI_C0402; MPN CL05B104KO5NNNC; LCSC C1525
C18: 10uF; C_0603_1608Metric; MPN CL10A106KP8NNNC; LCSC C19702
C19, C23: 4.7uF; RPI_C0402_wide; MPN CL05A475MP5NRNC; LCSC C23733
C24: 4.7uF; RPI_C0402; MPN CL05A475MP5NRNC; LCSC C23733
C25, C26: 15pF; C_0603_1608Metric; MPN CL10C150JB8NNNC; LCSC C1644
D2: BAT54C; SOT-23; MPN BAT54C,215; LCSC C37704
L1: 3.3uH; RPI_L_AOTA-B201610S3R3; MPN AOTA-B201610S3R3-101-T; LCSC C42411119
R18: 33R; RPI_R0402; MPN 0402WGF330JTCE; LCSC C25105
R19, R21, R23, R24: 1k; R_0603_1608Metric; MPN 0603WAF1001T5E; LCSC C21190
R20, R22: 10k; R_0603_1608Metric; MPN 0603WAF1002T5E; LCSC C25804
R25, R26: 27R; RPI_R0402; MPN 0402WGF270JTCE; LCSC C25100
SW1: BOOTSEL; SW_SPST_TS-1187A; MPN TS-1187A-B-A-B; LCSC C318884
SW2: RESET; SW_SPST_TS-1187A; MPN TS-1187A-B-A-B; LCSC C318884
TP8: SWCLK; TestPoint_Pad_D1.5mm
TP9: SWDIO; TestPoint_Pad_D1.5mm
TP10: GND; TestPoint_Pad_D1.5mm
TP11: RUN; TestPoint_Pad_D1.5mm
TP12: DVDD; TestPoint_Pad_D1.5mm
U1: RP2354B; QFN-80-1EP_10x10mm_P0.4mm_EP3.4x3.4mm; MPN RP2354B; LCSC C39843328
Y1: 12MHz; Crystal_SMD_3225-4Pin_3.2x2.5mm; MPN ABM8-272-T3; LCSC C20625731

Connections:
+3V3: C7.1, C8.1, C9.1, C10.1, C11.1, C12.1, C13.1, C14.1, C15.1, C16.1, C17.1, C18.1, C19.1, R18.1, R20.1, R22.1, U1.5 (IOVDD), U1.15 (IOVDD), U1.24 (IOVDD), U1.29 (IOVDD), U1.41 (IOVDD), U1.50 (IOVDD), U1.59 (ADC_AVDD), U1.60 (IOVDD), U1.64 (VREG_VIN), U1.68 (USB_OTP_VDD), U1.69 (QSPI_IOVDD), U1.76 (IOVDD); also elsewhere on the board
/BOOTSEL_CTL: R24.1; also elsewhere on the board
/RUN_CTL: R21.1; also elsewhere on the board
/S3_EN: D2.2; also elsewhere on the board
/USB_DM: R26.1; also elsewhere on the board
/USB_DP: R25.1; also elsewhere on the board
/rp-core/BOOTSEL_BTN: R23.2, SW1.1
/rp-core/QSPI_SS: R22.2, R23.1, R24.2, U1.75 (~QSPI_SS)
/rp-core/RP_LX: L1.2, U1.63 (VREG_LX)
/rp-core/RP_USB_DM: R26.2, U1.66 (USB_DM)
/rp-core/RP_USB_DP: R25.2, U1.67 (USB_DP)
/rp-core/RST_BTN: D2.3, SW2.1
/rp-core/RUN: D2.1, R20.2, R21.2, TP11.1, U1.35 (RUN)
/rp-core/SWCLK: TP8.1, U1.33 (SWCLK)
/rp-core/SWDIO: TP9.1, U1.34 (SWDIO)
/rp-core/VREG_AVDD: C24.1, R18.2, U1.61 (VREG_AVDD)
/rp-core/XIN: C25.1, U1.30 (XIN), Y1.1
/rp-core/XOUT: R19.1, U1.31 (XOUT)
/rp-core/XOUT_Y: C26.1, R19.2, Y1.3
DVDD: C20.1, C21.1, C22.1, C23.1, L1.1, TP12.1, U1.10 (DVDD), U1.32 (DVDD), U1.51 (DVDD), U1.65 (VREG_FB)
GND: C7.2, C8.2, C9.2, C10.2, C11.2, C12.2, C13.2, C14.2, C15.2, C16.2, C17.2, C18.2, C19.2, C20.2, C21.2, C22.2, C23.2, C24.2, C25.2, C26.2, SW1.2, SW2.2, TP10.1, U1.62 (VREG_PGND), U1.81 (GND), Y1.2 (G), Y1.4 (G); also elsewhere on the board

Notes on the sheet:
Supplies (RP2350 datasheet 6.3.7): IOVDD, QSPI_IOVDD, USB_OTP_VDD, ADC_AVDD and VREG_VIN on +3V3, the AP2112K LDO that rises with +5V; the core regulator switches VREG_LX through 3.3 uH onto DVDD (VREG_FB senses it), its analog supply VREG_AVDD through 33R / 4.7 uF. One 100 nF at every supply pin, 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
